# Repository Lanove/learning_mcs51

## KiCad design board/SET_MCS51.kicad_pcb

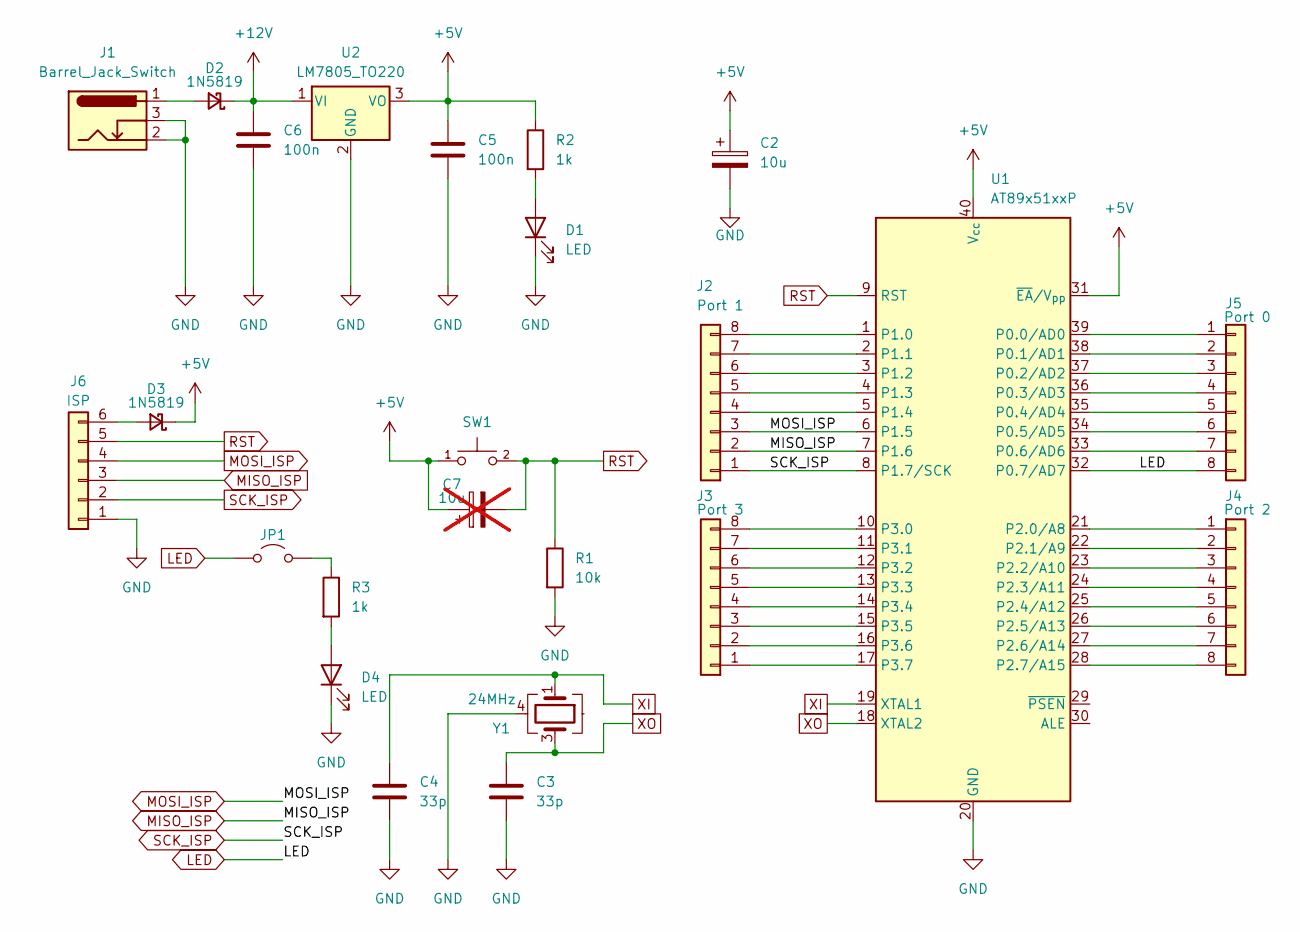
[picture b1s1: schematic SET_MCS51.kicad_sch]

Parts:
C2: 10u; CP_Radial_D5.0mm_P2.50mm
C3, C4: 33p; C_0805_2012Metric
C5, C6: 100n; C_0805_2012Metric
C7: 10u; C_0805_2012Metric; not fitted
D1, D4: LED; LED_D3.0mm
D2, D3: 1N5819; D_SOD-123F
J1: Barrel_Jack_Switch; BarrelJack_Wuerth_6941xx301002
J2: Port 1; PinHeader_1x08_P2.54mm_Vertical
J3: Port 3; PinHeader_1x08_P2.54mm_Vertical
J4: Port 2; PinHeader_1x08_P2.54mm_Vertical
J5: Port 0; PinHeader_1x08_P2.54mm_Vertical
J6: ISP; JST_XH_B6B-XH-AM_1x06_P2.50mm_Vertical
JP1: PinHeader_1x02_P2.54mm_Vertical
R1: 10k; R_0805_2012Metric
R2, R3: 1k; R_0805_2012Metric
SW1: TSA017A2526A; SW_PUSH_6mm; LCSC Part C2888433
U1: AT89x51xxP; DIP-40_W15.24mm
U2: LM7805_TO220; TO-220-3_Vertical
Y1: 24MHz; Crystal_SMD_3225-4Pin_3.2x2.5mm_HandSoldering

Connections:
+5V: C2.1, C5.1, C7.1, D3.1 (K), R2.1, SW1.1, U1.31 (~EA/V_{pp}), U1.40 (V_{cc}), U2.3 (VO)
+12V: C6.1, D2.1 (K), U2.1 (VI)
GND: C2.2, C3.2, C4.2, C5.2, C6.2, D1.1 (K), D4.1 (K), J1.2, J1.3, J6.1, R1.2, U1.20 (GND), U2.2 (GND), Y1.2, Y1.4
LED: J5.8, JP1.1 (A), U1.32 (P0.7/AD7)
MISO_ISP: J2.2, J6.3, U1.7 (P1.6)
MOSI_ISP: J2.3, J6.4, U1.6 (P1.5)
unnamed: D1.2 (A), R2.2
unnamed: D2.2 (A), J1.1
unnamed: D3.2 (A), J6.6
unnamed: D4.2 (A), R3.2
unnamed: J2.4, U1.5 (P1.4)
unnamed: J2.5, U1.4 (P1.3)
unnamed: J2.6, U1.3 (P1.2)
unnamed: J2.7, U1.2 (P1.1)
unnamed: J2.8, U1.1 (P1.0)
unnamed: J3.1, U1.17 (P3.7)
unnamed: J3.2, U1.16 (P3.6)
unnamed: J3.3, U1.15 (P3.5)
unnamed: J3.4, U1.14 (P3.4)
unnamed: J3.5, U1.13 (P3.3)
unnamed: J3.6, U1.12 (P3.2)
unnamed: J3.7, U1.11 (P3.1)
unnamed: J3.8, U1.10 (P3.0)
unnamed: J4.1, U1.21 (P2.0/A8)
unnamed: J4.2, U1.22 (P2.1/A9)
unnamed: J4.3, U1.23 (P2.2/A10)
unnamed: J4.4, U1.24 (P2.3/A11)
unnamed: J4.5, U1.25 (P2.4/A12)
unnamed: J4.6, U1.26 (P2.5/A13)
unnamed: J4.7, U1.27 (P2.6/A14)
unnamed: J4.8, U1.28 (P2.7/A15)
unnamed: J5.1, U1.39 (P0.0/AD0)
unnamed: J5.2, U1.38 (P0.1/AD1)
unnamed: J5.3, U1.37 (P0.2/AD2)
unnamed: J5.4, U1.36 (P0.3/AD3)
unnamed: J5.5, U1.35 (P0.4/AD4)
unnamed: J5.6, U1.34 (P0.5/AD5)
unnamed: J5.7, U1.33 (P0.6/AD6)
unnamed: JP1.2 (B), R3.1
RST: C7.2, J6.5, R1.1, SW1.2 (4), U1.9 (RST)
SCK_ISP: J2.1, J6.2, U1.8 (P1.7/SCK)
XI: C4.1, U1.19 (XTAL1), Y1.1
XO: C3.1, U1.18 (XTAL2), Y1.3

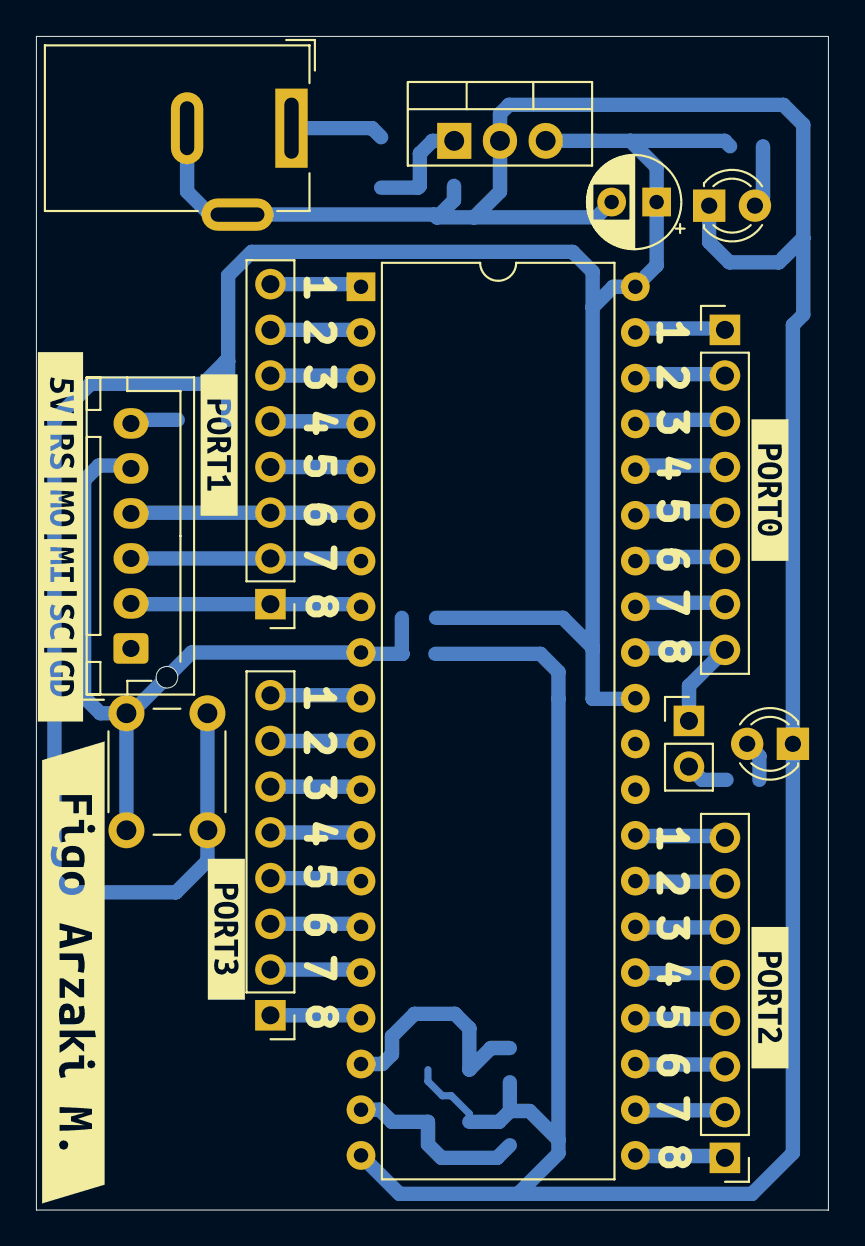
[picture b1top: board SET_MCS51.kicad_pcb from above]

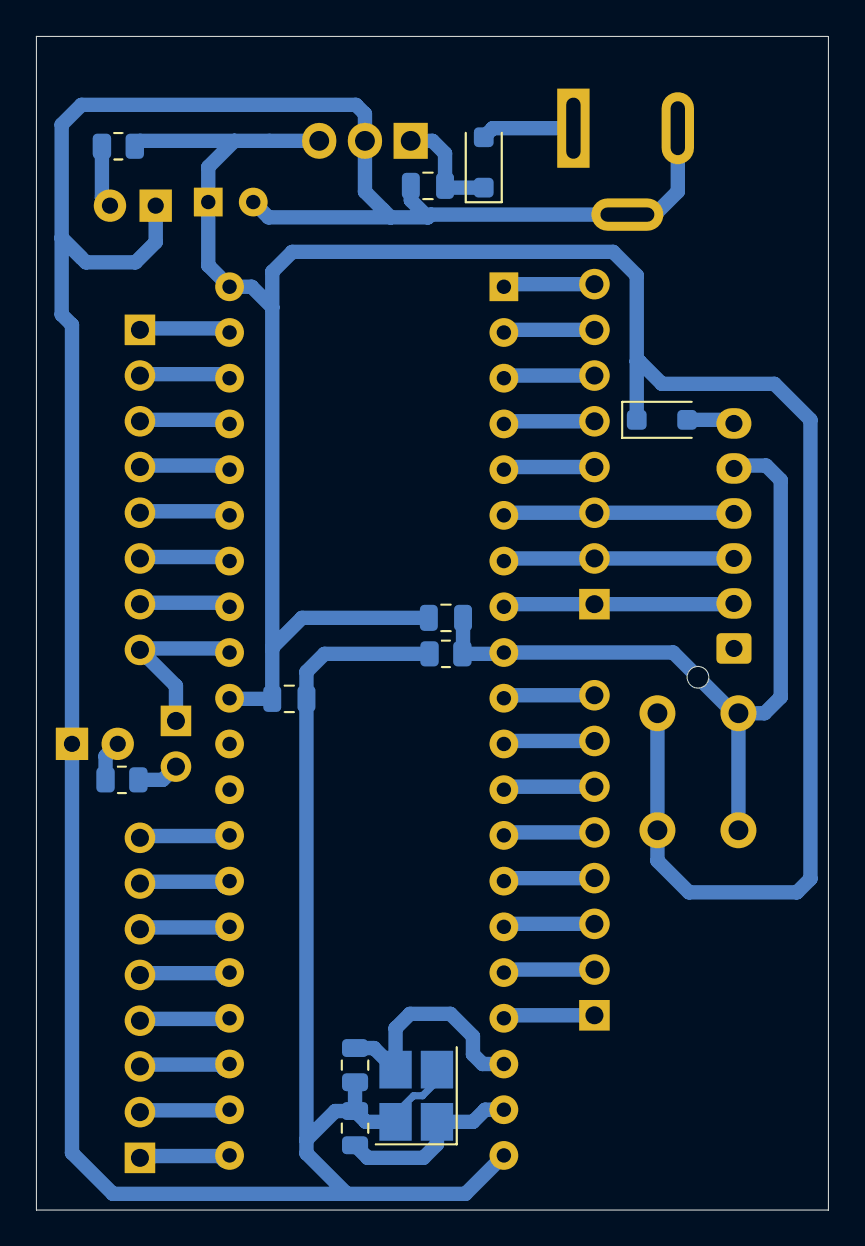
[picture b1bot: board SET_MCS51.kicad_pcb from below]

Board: 2 copper layers, 44.0 x 65.2 mm, 30 parts (11 on the bottom side), 43 nets.

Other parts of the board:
kibuzzard-66CF14A2: G***; kibuzzard-66CF14A2
kibuzzard-66CF14D0: G***; kibuzzard-66CF14D0
kibuzzard-66CF14EF: G***; kibuzzard-66CF14EF
kibuzzard-66CF150F: G***; kibuzzard-66CF150F
kibuzzard-66CF1473: G***; kibuzzard-66CF1473
kibuzzard-66D43124: G***; kibuzzard-66D43124

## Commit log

2024-10-10 Initial
2024-10-10 Removed unnecessary files Moved pdf to docs Moved board jpg to board Moved blinker asm to blinker
2024-10-10 minor refactor on note.asm
2024-10-30 week 9 and 10, lcd, lm35 and mpu6050
2024-11-21 W13 WIP
2024-11-21 W13 DDS done
2024-12-19 lulus
